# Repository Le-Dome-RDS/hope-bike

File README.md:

# hope-bike
An open source Pedalling Assistant Sytem for 26" wheeled bikes 

Licence : CC-BY-SA

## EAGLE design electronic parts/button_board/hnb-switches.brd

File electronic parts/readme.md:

#Electronic parts

This folder contains datasheet, eagle project and schematic for the three different PCB files : 

* the button card that contains the three buttons used for the control of the speed by the user,
* the command card that contains LEDs used to visualize both the battery level and the speed assist level. It also contains the arduino board.
*  the power management card that contains all the power electronic stuff necessary to drive the brushless motor using the electrical power battery.

The datasheets for the electronical devices used in the cards and the commercial items required for the kit (battery, motor and the pedal sensor) are also avalaible

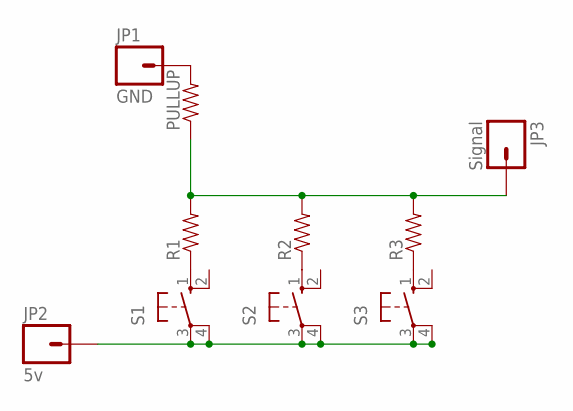
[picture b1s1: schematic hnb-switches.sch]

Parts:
JP1: GND; 1X01_LONGPAD
JP2: 5v; 1X01_LONGPAD
JP3: Signal; 1X01_LONGPAD
PULLUP: RESISTOR1206; 1206
R1, R2, R3: RESISTOR1206; 1206
S1, S2, S3: 10-XX; B3F-10XX

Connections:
unnamed: JP1.1, PULLUP.2
unnamed: R1.1, S1.1 (S)
unnamed: R2.1, S2.1 (S)
unnamed: R3.1, S3.1 (S)
unnamed: JP3.1, PULLUP.1, R1.2, R2.2, R3.2
unnamed: JP2.1, S1.3, S1.4 (P1), S2.3, S2.4 (P1), S3.3, S3.4 (P1)

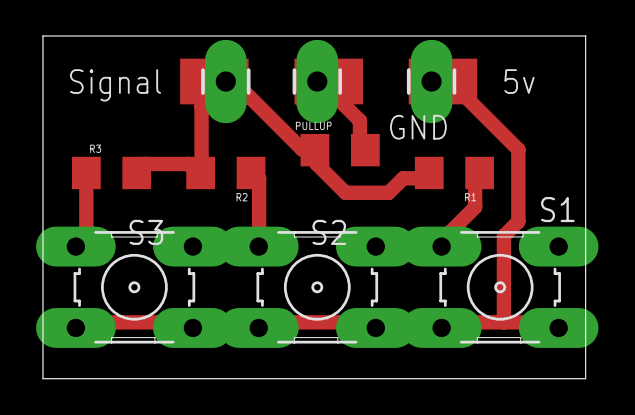
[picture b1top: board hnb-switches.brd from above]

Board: 2 copper layers, 30.2 x 19.0 mm, 10 parts (0 on the bottom side), 6 nets.

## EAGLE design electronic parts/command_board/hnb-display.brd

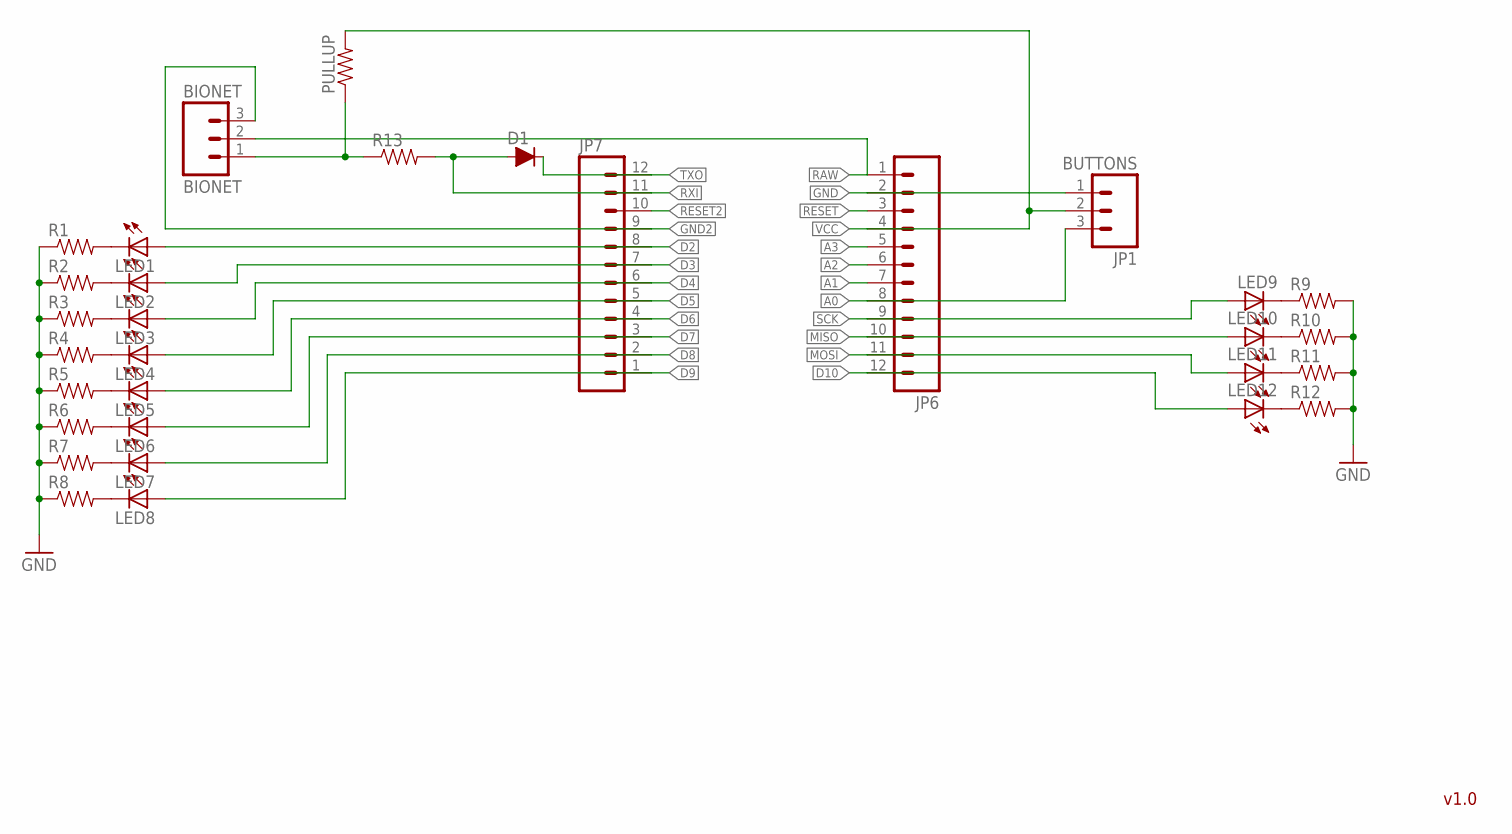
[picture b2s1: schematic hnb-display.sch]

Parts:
BIONET: BIONET; 1X03
D1: D-FILL-SOD-80; SOD80
JP1: BUTTONS; 1X03
JP6, JP7: M12PTH; 1X12
LED1, LED2, LED3, LED4, LED5, LED6, LED7, LED8, LED9, LED10, LED11, LED12: LEDSMT1206; 1206
PULLUP: RESISTOR1206; 1206
R1, R2, R3, R4, R5, R6, R7, R8, R9, R10, R11, R12, R13: RESISTOR1206; 1206

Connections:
A0: JP1.3, JP6.8
A1: JP6.7
A2: JP6.6
A3: JP6.5
D2: JP7.8, LED1.A
D3: JP7.7, LED2.A
D4: JP7.6, LED3.A
D5: JP7.5, LED4.A
D6: JP7.4, LED5.A
D7: JP7.3, LED6.A
D8: JP7.2, LED7.A
D9: JP7.1, LED8.A
D10: JP6.12, LED12.A
GND: JP1.1, JP6.2, R1.1, R2.1, R3.1, R4.1, R5.1, R6.1, R7.1, R8.1, R9.2, R10.2, R11.2, R12.2
GND2: BIONET.3, JP7.9
MISO: JP6.10, LED10.A
MOSI: JP6.11, LED11.A
unnamed: LED1.C, R1.2
unnamed: LED2.C, R2.2
unnamed: LED3.C, R3.2
unnamed: LED4.C, R4.2
unnamed: LED5.C, R5.2
unnamed: LED6.C, R6.2
unnamed: LED7.C, R7.2
unnamed: LED8.C, R8.2
unnamed: LED12.C, R12.1
unnamed: LED10.C, R10.1
unnamed: LED11.C, R11.1
unnamed: LED9.C, R9.1
unnamed: BIONET.1, PULLUP.1, R13.1
RAW: BIONET.2, JP6.1
RESET: JP6.3
RESET2: JP7.10
RXI: D1.2 (A), JP7.11, R13.2
SCK: JP6.9, LED9.A
TXO: D1.1 (C), JP7.12
VCC: JP1.2, JP6.4, PULLUP.2

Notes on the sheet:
v1.0

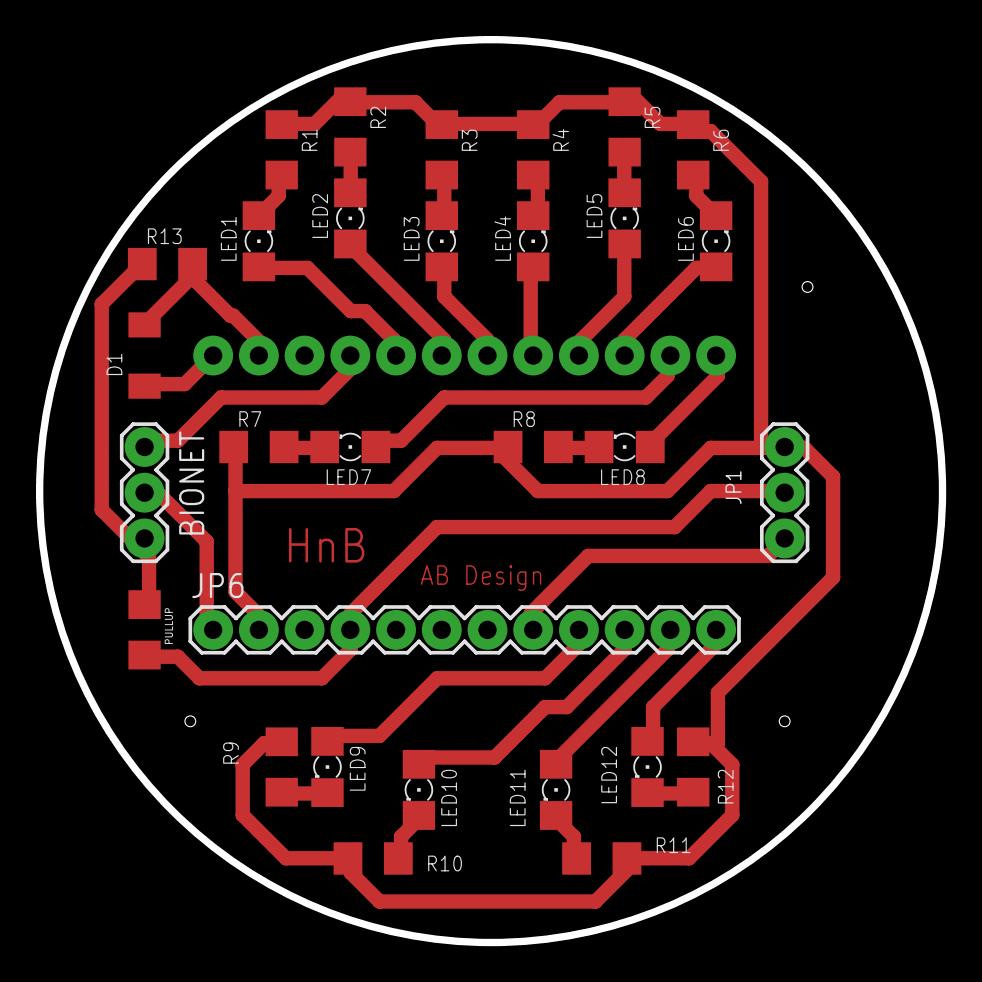
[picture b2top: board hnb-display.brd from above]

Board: 2 copper layers, 50.2 x 50.2 mm, 32 parts (1 on the bottom side), 32 nets.

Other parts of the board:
U$1: A5L-LOC

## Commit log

2016-10-20 First commit with JMR
    Data sheet and other documentations
2016-10-20 add read me to electronic
2016-10-20 test by JMR
    To be deleted
2017-01-19 adding folder structure and read-me files
    To start with the 18th of January work session.
2017-01-19 source code for the command card and the power management card
2017-01-19 readme.md updates
    Update of few readme.md
2017-01-19 pdf...
    pdf files for the schematic and the pcb of the different electronic card
2017-01-19 documents maj
    Modification in Readme, odt files of the doc
2017-01-19 update docs
2017-01-19 BOM renaming
2017-01-19 BOM fastenings
2017-02-24 - New code for the command card based on the work of Gaylord Lebrun and Medhi Brinis. - a report (in french) is provided in the documents section that explains how the command works.
2017-02-24 - correction in the DC00_architecture document
2017-02-24 Remove of .webloc (apple only) and description of web link in the readme.md files.
2017-03-15 documentation update
    Mainly document update to programm the boards
2017-03-15 Mise à jour code carte commande
    Mise à jour de la machine d'état pour une gestion plus fine des
    dépassements du courant MAX
2017-03-17 Documentation update
    User manuel
    diy manual
    certificate
2017-03-17 Last update before DIY workshop
    Doc updates
2020-01-31 HnB hardware version 2 directory creation for command card programming
2020-01-31 Readme.md update
2020-01-31 cleanup for stating software command for v2 hardware
2020-02-03 test
2020-02-03 Ajout des variables globales
2020-02-03 rename filename and starts heltec32 integration
2020-02-24 Integration of the command lines for the v2 electronic device
2020-02-24 nightly updates
2020-02-26 after two days working on the code
2020-03-02 still one bug to solve
2020-03-10 version après premier atelier montage au dôme
2020-07-23 vecy close to the final version before going in holidays
2021-03-03 2021 update : new state to slow down quietly the motor, button update
2021-03-04 2021 03 04 update : median filter for the measurements of the bike speed
2021-03-22 2021 03 22 : motor stop detection. Modulation of the deltaPWM with the current
2021-03-24 2021 03 25 : better motor stop detection and more precise PWM moduluation ; screen ajustement ; special keyboard option update
2021-04-13 version 1.99. La version 2.0 est presque, mais alors presque, terminée. Et Yohoho et une bouteille de rhum.
2021-04-14 integration des plans openscad
2021-04-15 integration des plans pour le capteur de hall de la roue
2021-04-15 Optimisation des boitiers
2021-04-15 Optimisation des boitiers, suite

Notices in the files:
parts and their libraries:
SparkFun-Passives: Licensing: Creative Commons ShareAlike 4.0 International - https://creativecommons.org/licenses/by-sa/4.0
